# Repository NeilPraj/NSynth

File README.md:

# NSynth
My synthesizer projects.

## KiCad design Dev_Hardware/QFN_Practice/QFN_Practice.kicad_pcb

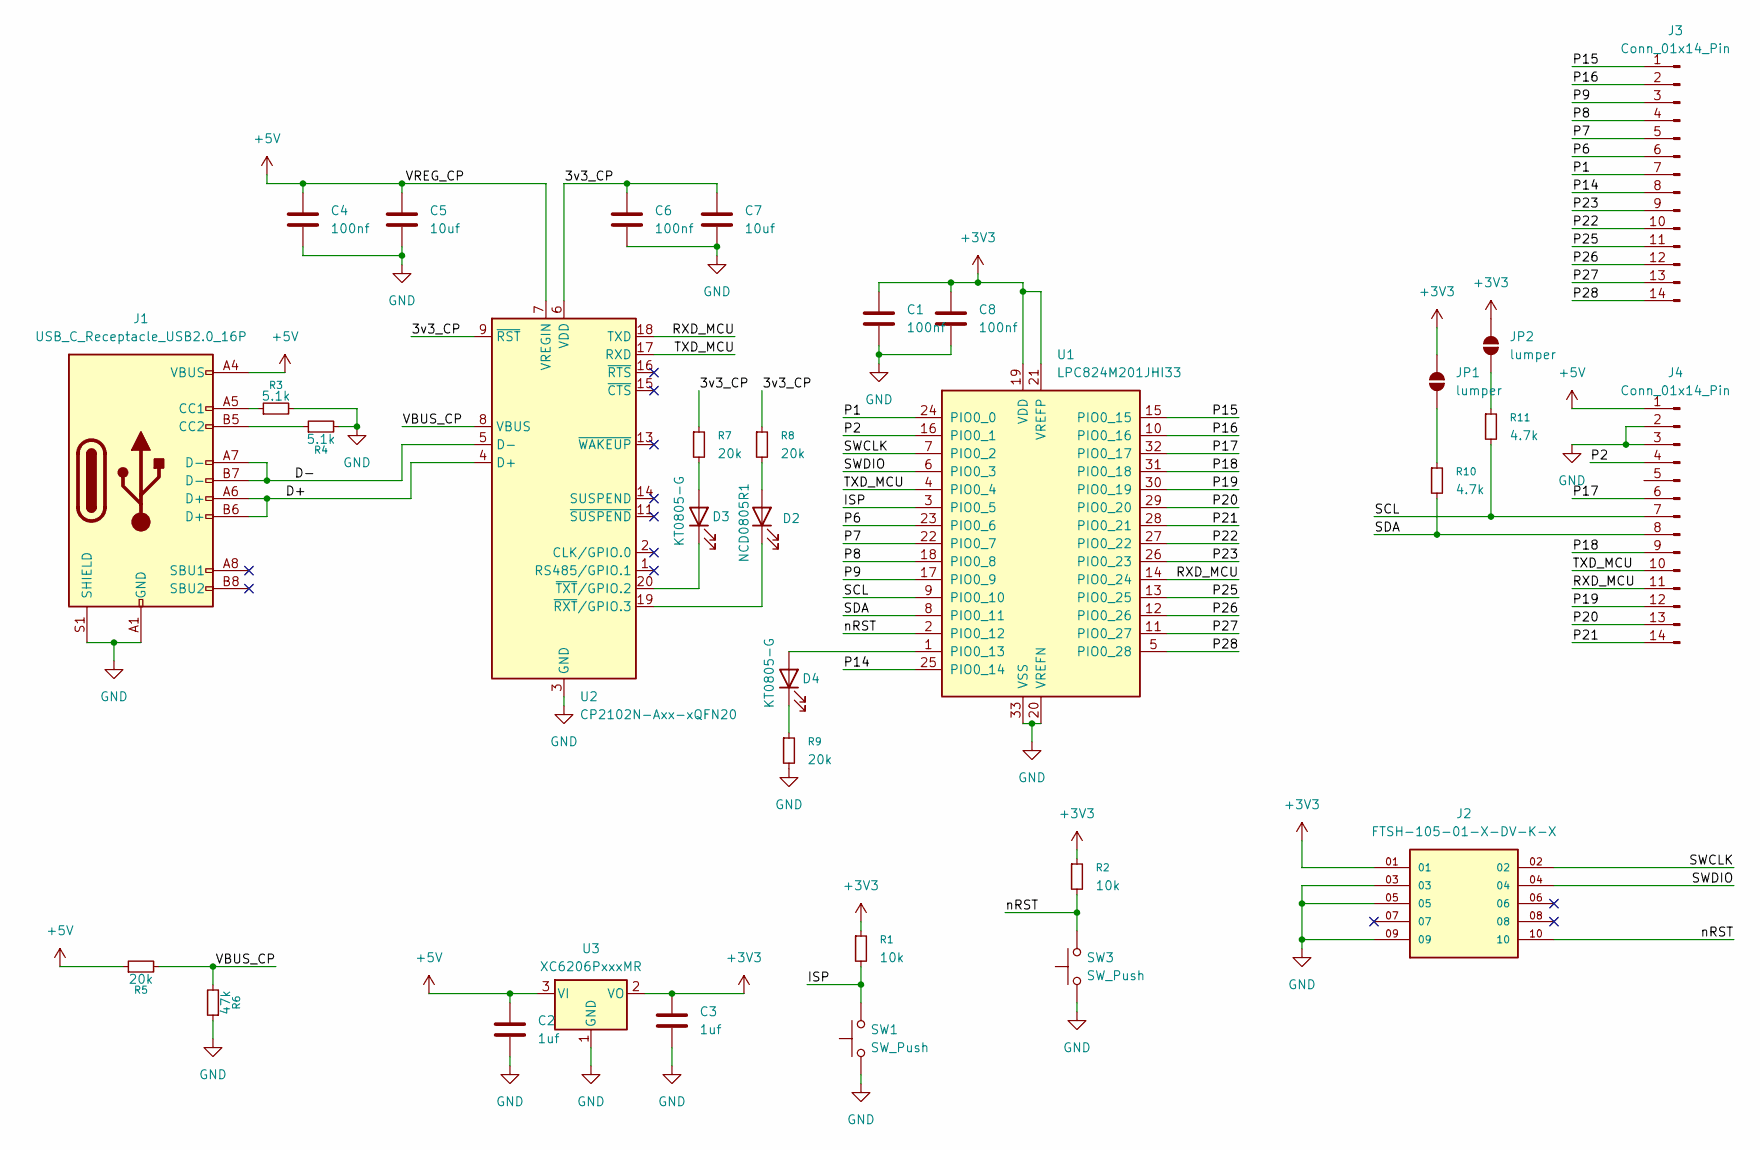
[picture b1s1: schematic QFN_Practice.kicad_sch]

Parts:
C1, C4, C6, C8: 100nf; C_0603_1608Metric
C2, C3: 1uf; C_0603_1608Metric
C5, C7: 10uf; C_0603_1608Metric
D2: NCD0805R1; LED_0805_2012Metric
D3, D4: KT0805-G; LED_0805_2012Metric
J1: USB_C_Receptacle_USB2.0_16P; USB_C_Receptacle_G-Switch_GT-USB-7010ASV
J2: FTSH-105-01-X-DV-K-X; SAMTEC_FTSH-105-01-X-DV-K-X; PARTREV H
J3, J4: Conn_01x14_Pin; PinHeader_1x14_P2.54mm_Vertical
JP1, JP2: lumper; SolderJumper-2_P1.3mm_Open_RoundedPad1.0x1.5mm
R1, R2: 10k; R_0603_1608Metric
R3, R4: 5.1k; R_0603_1608Metric
R5, R7, R8, R9: 20k; R_0603_1608Metric
R6: 47k; R_0603_1608Metric
R10, R11: 4.7k; R_0603_1608Metric
SW1, SW3: SW_Push; SW_SPST_TS-1088-xR020
U1: LPC824M201JHI33; QFN-32-1EP_5x5mm_P0.5mm_EP3.45x3.45mm
U2: CP2102N-Axx-xQFN20; SiliconLabs_QFN-20-1EP_3x3mm_P0.5mm_EP1.8x1.8mm
U3: XC6206PxxxMR; SOT-23-3

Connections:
+3V3: C1.1, C3.1, C8.1, J2.01, JP1.2 (B), JP2.2 (B), R1.1, R2.1, U1.19 (VDD), U1.21 (VREFP), U3.2 (VO)
+5V: C2.1, C4.1, C5.1, J1.A4 (VBUS), J1.A9 (VBUS), J1.B4 (VBUS), J1.B9 (VBUS), J4.1, R5.1, U2.7 (VREGIN), U3.3 (VI)
/3v3_CP: C6.1, C7.1, R7.1, R8.1, U2.6 (VDD), U2.9 (~RST)
/D+: J1.A6 (D+), J1.B6 (D+), U2.4 (D+)
/D-: J1.A7 (D-), J1.B7 (D-), U2.5 (D-)
/ISP: R1.2, SW1.2, U1.3 (PIO0_5)
/P1: J3.7, U1.24 (PIO0_0)
/P2: J4.4, U1.16 (PIO0_1)
/P6: J3.6, U1.23 (PIO0_6)
/P7: J3.5, U1.22 (PIO0_7)
/P8: J3.4, U1.18 (PIO0_8)
/P9: J3.3, U1.17 (PIO0_9)
/P14: J3.8, U1.25 (PIO0_14)
/P15: J3.1, U1.15 (PIO0_15)
/P16: J3.2, U1.10 (PIO0_16)
/P17: J4.6, U1.32 (PIO0_17)
/P18: J4.9, U1.31 (PIO0_18)
/P19: J4.12, U1.30 (PIO0_19)
/P20: J4.13, U1.29 (PIO0_20)
/P21: J4.14, U1.28 (PIO0_21)
/P22: J3.10, U1.27 (PIO0_22)
/P23: J3.9, U1.26 (PIO0_23)
/P25: J3.11, U1.13 (PIO0_25)
/P26: J3.12, U1.12 (PIO0_26)
/P27: J3.13, U1.11 (PIO0_27)
/P28: J3.14, U1.5 (PIO0_28)
/RXD_MCU: J4.11, U1.14 (PIO0_24), U2.18 (TXD)
/SCL: J4.7, R11.2, U1.9 (PIO0_10)
/SDA: J4.8, R10.2, U1.8 (PIO0_11)
/SWCLK: J2.02, U1.7 (PIO0_2)
/SWDIO: J2.04, U1.6 (PIO0_3)
/TXD_MCU: J4.10, U1.4 (PIO0_4), U2.17 (RXD)
/VBUS_CP: R5.2, R6.2, U2.8 (VBUS)
/nRST: J2.10, R2.2, SW3.2, U1.2 (PIO0_12)
GND: C1.2, C2.2, C3.2, C4.2, C5.2, C6.2, C7.2, C8.2, J1.A1 (GND), J1.A12 (GND), J1.B1 (GND), J1.B12 (GND), J1.S1 (SHIELD), J2.03, J2.05, J2.09, J4.2, J4.3, R3.2, R4.2, R6.1, R9.2, SW1.1, SW3.1, U1.20 (VREFN), U1.33 (VSS), U2.3 (GND), U2.12 (GND), U2.21 (GND), U3.1 (GND)
unnamed: D2.2 (A), R8.2
unnamed: D2.1 (K), U2.19 (~RXT/GPIO.3)
unnamed: D3.2 (A), R7.2
unnamed: D3.1 (K), U2.20 (~TXT/GPIO.2)
unnamed: D4.2 (A), U1.1 (PIO0_13)
unnamed: D4.1 (K), R9.1
unnamed: J1.A5 (CC1), R3.1
unnamed: J1.B5 (CC2), R4.1
unnamed: JP1.1 (A), R10.1
unnamed: JP2.1 (A), R11.1

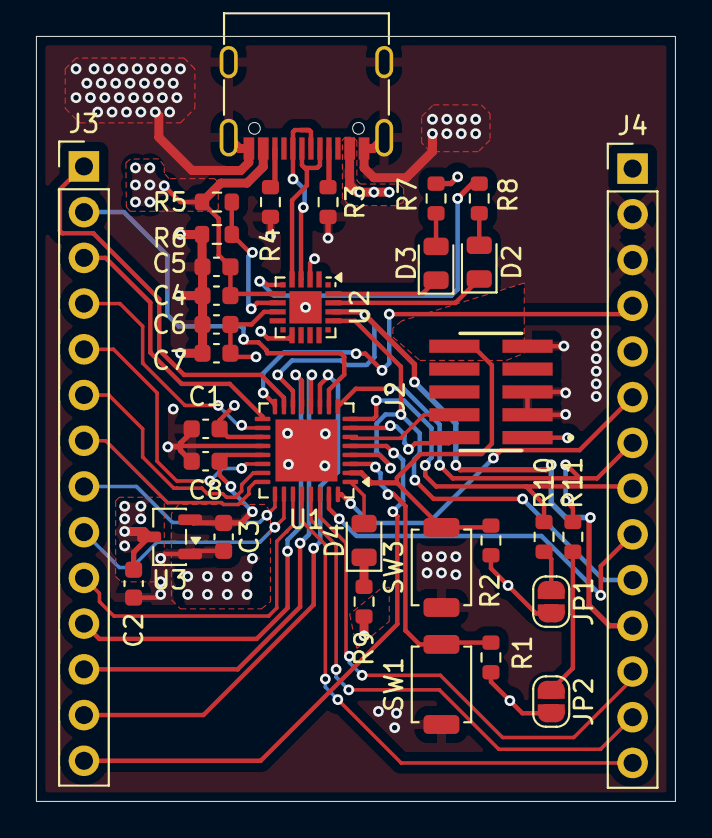
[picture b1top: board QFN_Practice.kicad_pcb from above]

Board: 4 copper layers, 35.5 x 42.5 mm, 33 parts (0 on the bottom side), 45 nets.

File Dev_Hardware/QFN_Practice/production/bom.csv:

Designator,Footprint,Quantity,Value,LCSC Part #
"C1, C4, C6, C8",0603,4,100nf,
"C2, C3",0603,2,1uf,
"C5, C7",0603,2,10uf,
D2,0805,1,NCD0805R1,
"D3, D4",0805,2,KT0805-G,
J1,USB_C_Receptacle_G-Switch_GT-USB-7010ASV,1,USB_C_Receptacle_USB2.0_16P,
J2,SAMTEC_FTSH-105-01-X-DV-K-X,1,FTSH-105-01-X-DV-K-X,
"J3, J4",PinHeader_1x14_P2.54mm_Vertical,2,Conn_01x14_Pin,
"R1, R2",0603,2,10k,
"R10, R11",0603,2,4.7k,
"R3, R4",0603,2,5.1k,
"R5, R7, R8, R9",0603,4,20k,
R6,0603,1,47k,
"SW1, SW3",SW_SPST_TS-1088-xR020,2,SW_Push,
U1,QFN-32-1EP_5x5mm_P0.5mm_EP3.45x3.45mm,1,LPC824M201JHI33,
U2,SiliconLabs_QFN-20-1EP_3x3mm_P0.5mm_EP1.8x1.8mm,1,CP2102N-Axx-xQFN20,
U3,SOT-23-3,1,XC6206PxxxMR,

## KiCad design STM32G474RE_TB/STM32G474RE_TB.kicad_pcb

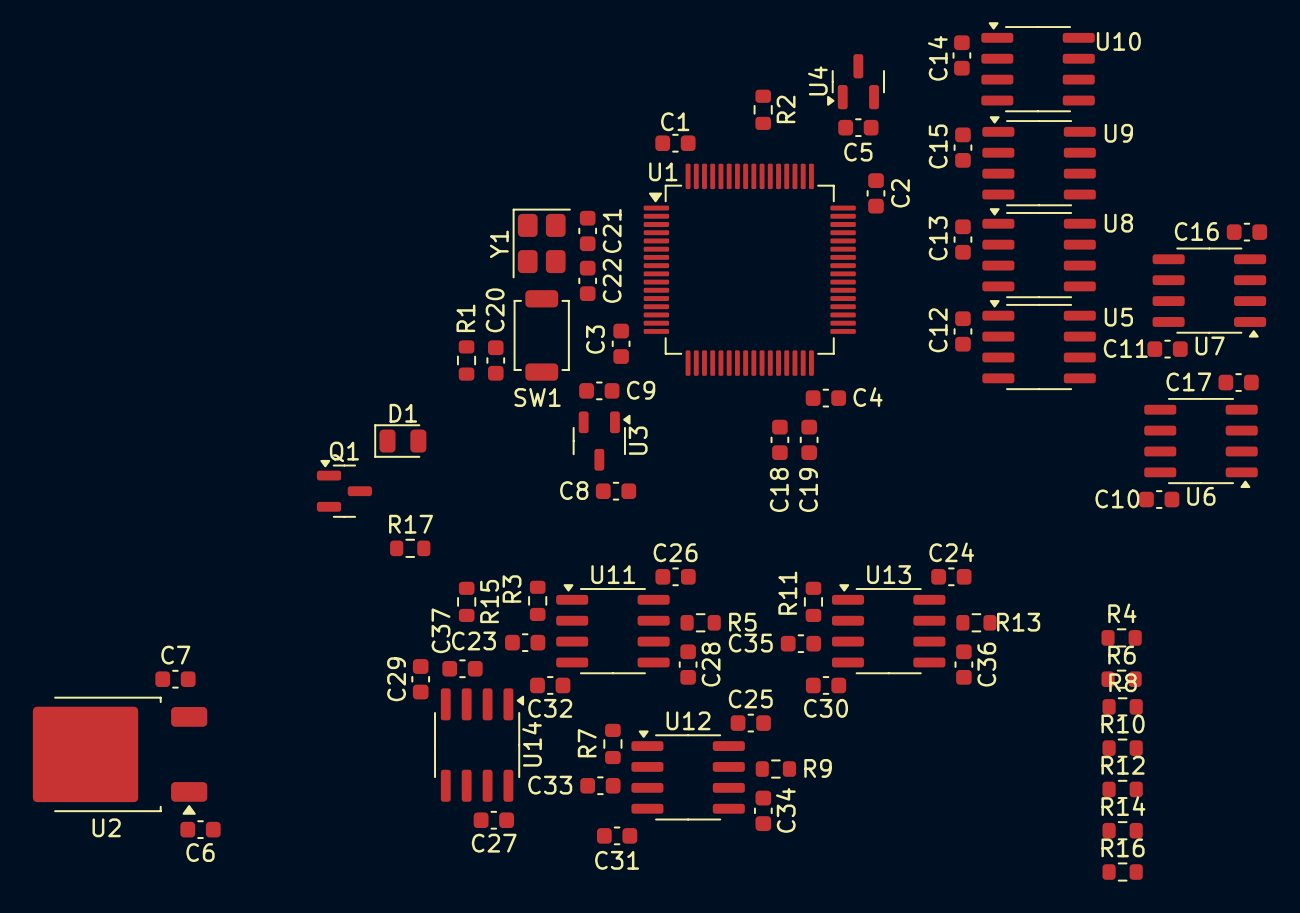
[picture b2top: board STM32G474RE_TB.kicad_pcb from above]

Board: 2 copper layers, 72 parts (0 on the bottom side), 47 nets, no tracks yet.

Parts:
C1, C2, C3, C4: 100nF; C_0603_1608Metric
C5: 0.47uF; C_0603_1608Metric
C6: 0.33uf; C_0603_1608Metric
C7, C10, C11, C12, C13, C14, C15, C16, C17, C18, C20, C24, C25, C26, C27, C29, C30, C31, C32: 0.1uf; C_0603_1608Metric
C8, C9: 1u; C_0603_1608Metric
C19: 1uf; C_0603_1608Metric
C21, C22: 22pf; C_0603_1608Metric
C23, C28, C33, C34, C35: 330nF; C_0603_1608Metric
C36, C37: 33nf; C_0603_1608Metric
D1: XL-2012UBC; LED_0805_2012Metric
Q1: 2N7002; SOT-23
R1: 10k; R_0603_1608Metric
R2: 100k; R_0603_1608Metric
R3, R5, R7, R9, R11, R13, R15, R17: 220; R_0603_1608Metric
R4, R6, R8, R10, R12, R14, R16: 1k; R_0603_1608Metric
SW1: TS-1088-AR02016; SW_SPST_TS-1088-xR025
U1: STM32G474RETx; LQFP-64_10x10mm_P0.5mm
U2: L7805; TO-252-2
U3: XC6206P332MR-G; SOT-23-3
U4: REF3125; SOT-23
U5, U8, U9, U10: MCP4921-ESN; SOIC-8_3.9x4.9mm_P1.27mm
U6, U7, U11, U12, U13, U14: OPA1678; SOIC-8_3.9x4.9mm_P1.27mm
Y1: ABM8G-24.000MHZ-18-D2Y-T; Crystal_SMD_Abracon_ABM8G-4Pin_3.2x2.5mm

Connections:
+2V5REF: C18.1, C19.1, U1.28 (VREF+), U4.2 (OUT), U5.6 (VrefA), U8.6 (VrefA), U9.6 (VrefA), U10.6 (VrefA)
+3.3V: C1.2, C2.2, C3.2, C4.2, C5.1, C9.2, R1.1, U1.1 (VBAT), U1.16 (VDD), U1.29 (VDDA), U1.32 (VDD), U1.48 (VDD), U1.64 (VDD), U3.2 (VO), U4.1 (IN)
+5V: C7.2, C8.2, C12.1, C13.1, C14.1, C15.1, R17.2, U2.3 (OUT), U3.3 (VI), U5.1 (VDD), U8.1 (VDD), U9.1 (VDD), U10.1 (VDD)
+12V: C6.2, C10.1, C11.1, C24.1, C25.1, C26.1, C27.1, U2.1 (IN), U6.8 (V+), U7.8 (V+), U11.8 (V+), U12.8 (V+), U13.8 (V+), U14.8 (V+)
-12V: C16.1, C17.1, C29.1, C30.1, C31.1, C32.1, U6.4 (V-), U7.4 (V-), U11.4 (V-), U12.4 (V-), U13.4 (V-), U14.4 (V-)
/DAC1_CS: U1.38 (PC6), U5.2 (~CS)
/DAC2_CS: U1.39 (PC7), U8.2 (~CS)
/DAC3_CS: U1.40 (PC8), U9.2 (~CS)
/DAC4_CS: U1.41 (PC9), U10.2 (~CS)
/MCU_CONFIG/NRST: C20.1, R1.2, SW1.2, U1.7 (PG10)
/MCU_CONFIG/PD2/BOOT0: R2.2, U1.55 (PD2)
/MCU_CONFIG/XOSC1: C21.1, U1.5 (PF0), Y1.1
/MCU_CONFIG/XOSC2: C22.1, U1.6 (PF1), Y1.3
/SPI1_DACs/DAC1_OUT: U6.1, U6.2 (-)
/SPI1_DACs/DAC1_out_nobuf: U5.8 (VoutA), U6.3 (+)
/SPI1_DACs/DAC2_OUT: U6.6 (-), U6.7
/SPI1_DACs/DAC2_out_nobuf: U6.5 (+), U8.8 (VoutA)
/SPI1_DACs/DAC3_OUT: U7.1, U7.2 (-)
/SPI1_DACs/DAC3_out_nobuf: U7.3 (+), U9.8 (VoutA)
/SPI1_DACs/DAC4_OUT: U7.6 (-), U7.7
/SPI1_DACs/DAC4_out_nobuf: U7.5 (+), U10.8 (VoutA)
/SPI1_MOSI: U1.37 (PB15), U5.3 (SCK), U8.3 (SCK), U9.3 (SCK), U10.3 (SCK)
/SPI1_SCK: U1.35 (PB13), U5.4 (SDI), U8.4 (SDI), U9.4 (SDI), U10.4 (SDI)
/STDAC1_C1_OUT: R3.1, U1.18 (PA4)
/STDAC1_C2_OUT: R5.1, U1.19 (PA5)
/STDAC2_OUT: R7.1, U1.20 (PA6)
/STDAC3_C1_OUT: R9.1, U1.14 (PA2)
/STDAC3_C2_OUT: R11.1, U1.25 (PB1)
/STDAC4_C1_OUT: R13.1, U1.34 (PB12)
/STDAC4_C2_OUT: R15.1, U1.42 (PA8)
GND: C1.1, C2.1, C3.1, C4.1, C5.2, C6.1, C7.1, C8.1, C9.1, C10.2, C11.2, C12.2, C13.2, C14.2, C15.2, C16.2, C17.2, C18.2, C19.2, C20.2, C21.2, C22.2, C23.2, C24.2, C25.2, C26.2, C27.2, C28.2, C29.2, C30.2, C31.2, C32.2, C33.2, C34.2, C35.2, C36.2, C37.2, Q1.2 (S), R2.1, SW1.1, U1.15 (VSS), U1.27 (VSSA), U1.31 (VSS), U1.47 (VSS), U1.63 (VSS), U2.2 (GND), U3.1 (GND), U4.3 (GND), U5.5 (~LDAC), U5.7 (AVSS), U8.5 (~LDAC), U8.7 (AVSS), U9.5 (~LDAC), U9.7 (AVSS), U10.5 (~LDAC), U10.7 (AVSS), Y1.2 (GND), Y1.4 (GND__1)
unnamed: D1.2 (A), R17.1
unnamed: D1.1 (K), Q1.3 (D)
unnamed: C23.1, R3.2, U11.3 (+)
unnamed: R4.1, U11.1, U11.2 (-)
unnamed: C28.1, R5.2, U11.5 (+)
unnamed: R6.1, U11.6 (-), U11.7
unnamed: C33.1, R7.2, U12.3 (+)
unnamed: R8.1, U12.1, U12.2 (-)
unnamed: C34.1, R9.2, U12.5 (+)
unnamed: R10.1, U12.6 (-), U12.7
unnamed: C35.1, R11.2, U13.3 (+)
unnamed: R12.1, U13.1, U13.2 (-)
unnamed: C36.1, R13.2, U13.5 (+)
unnamed: R14.1, U13.6 (-), U13.7
unnamed: C37.1, R15.2, U14.3 (+)
unnamed: R16.1, U14.1, U14.2 (-)

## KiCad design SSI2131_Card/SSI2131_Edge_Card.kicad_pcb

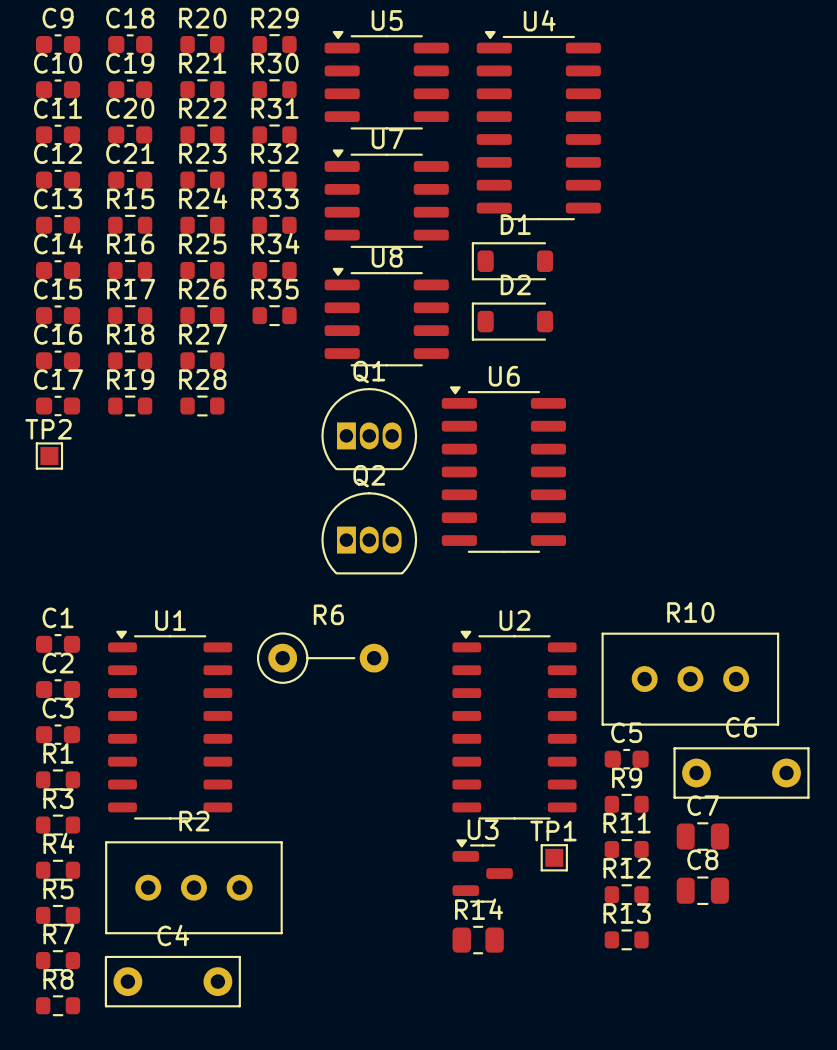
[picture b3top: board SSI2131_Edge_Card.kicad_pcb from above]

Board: 2 copper layers, 70 parts (0 on the bottom side), 43 nets, no tracks yet.

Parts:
C1, C5: 220nF; C_0603_1608Metric
C2, C3: 10n; C_0603_1608Metric
C4, C6: 3.9nf; C_Rect_L7.2mm_W2.5mm_P5.00mm_FKS2_FKP2_MKS2_MKP2
C7, C8: 1uf; C_0805_2012Metric
C9, C18: 1nF; C_0603_1608Metric
C10, C19: 470nF; C_0603_1608Metric
C11, C12, C13, C14, C15, C16, C17, C20, C21: 0.1uf; C_0603_1608Metric
D1, D2: 1N4148W; D_SOD-123
Q1, Q2: 2N3906; TO-92_Inline
R1, R9: 100k; R_0603_1608Metric
R2, R10: 5k; Potentiometer_Bourns_3296W_Vertical
R3, R8, R11, R15, R23: 10k; R_0603_1608Metric
R4, R12: 680; R_0603_1608Metric
R5, R13: 20k; R_0603_1608Metric
R6: 267k; R_Axial_DIN0207_L6.3mm_D2.5mm_P5.08mm_Vertical
R7: 4.3k; R_0603_1608Metric
R14: 2k; R_0805_2012Metric
R16, R24: 2.5k; R_0603_1608Metric
R17, R26: 6.8k; R_0603_1608Metric
R18, R29: 33k; R_0603_1608Metric
R19, R30: 120k; R_0603_1608Metric
R20, R31: 3.9k; R_0603_1608Metric
R21, R22, R25, R27, R28, R32, R33, R34, R35: 1k; R_0603_1608Metric
TP1: 2V5 TP; TestPoint_Pad_1.0x1.0mm
TP2: PMOD_TP; TestPoint_Pad_1.0x1.0mm
U1, U2: SSI2131; STC_SOP-16_3.9x9.9mm_P1.27mm
U3: LM4040DBZ-2.5; SOT-23
U4: LM13700; SOIC-16_3.9x9.9mm_P1.27mm
U5, U7, U8: OPA1678; SOIC-8_3.9x4.9mm_P1.27mm
U6: CD4066BM; SOIC-14_3.9x8.7mm_P1.27mm

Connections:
+2V5: C7.1, C8.1, R1.2, R2.1, R9.2, R10.1, R14.2, TP1.1, U3.1 (K)
+5V: C11.1, C12.1, C13.1, C14.1, C20.1, R14.1, U4.11 (V+), U5.8 (V+), U6.14 (VDD), U7.8 (V+), U8.8 (V+)
-12V: C15.1, C16.1, C17.1, C21.1, U4.6 (V-), U5.4 (V-), U7.4 (V-), U8.4 (V-)
/B_EXPO_IN: R9.1, R11.2, R13.2, U2.6 (EXPO_FREQ)
/OSC A/A_EXPO_IN: R1.1, R3.2, R6.2, R18.2, TP2.1, U1.6 (EXPO_FREQ), U5.7
/OSC A/PWM_MOD_IN: R27.2, U8.1
GND: C1.2, C4.2, C5.2, C7.2, C8.2, C11.2, C12.2, C13.2, C14.2, C15.2, C16.2, C17.2, C20.2, C21.2, R2.3, R7.1, R8.1, R10.3, R21.1, R22.1, R34.1, R35.1, U3.2 (A), U5.3 (+), U5.5 (+), U6.7 (VSS), U7.3 (+), U7.5 (+), U8.3 (+), U8.5 (+)
unnamed: C1.1, R4.2, R5.1
unnamed: C5.1, R12.2, R13.1
unnamed: C10.1, U6.2
unnamed: C10.2, R19.1
unnamed: C19.1, U6.3
unnamed: C19.2, R30.1
unnamed: C9.2, D1.2 (A), Q1.1 (E)
unnamed: C9.1, D1.1 (K), R16.1, U5.2 (-)
unnamed: C18.2, D2.2 (A), Q2.1 (E)
unnamed: C18.1, D2.1 (K), R24.1, U7.2 (-)
unnamed: Q1.2 (B), U5.1
unnamed: Q1.3 (C), R17.1
unnamed: Q2.2 (B), U7.1
unnamed: Q2.3 (C), R26.1
unnamed: R2.2, R3.1
unnamed: R10.2, R11.1
unnamed: R15.1, R16.2
unnamed: R17.2, U4.16
unnamed: R19.2, R20.1
unnamed: R23.1, R24.2
unnamed: R26.2, U4.1
unnamed: R28.2, R32.1, U8.7
unnamed: R29.2, R33.2, U7.7
unnamed: R30.2, R31.1
unnamed: C3.2, R8.2, U1.10 (HARD_SYNC)
unnamed: R6.1, R7.2, U1.5 (HF_TRACK)
unnamed: C2.2, U1.11 (SOFT_SYNC)
unnamed: C4.1, U1.8 (TCAP)
unnamed: R22.2, U4.14 (+)
unnamed: R20.2, R21.2, U4.13 (-)
unnamed: R35.2, U4.3 (+)
unnamed: R31.2, R34.2, U4.4 (-)
unnamed: R18.1, U4.12, U5.6 (-)
unnamed: R29.1, U4.5, U7.6 (-)
unnamed: R27.1, R32.2, U8.2 (-)
unnamed: R25.2, R28.1, R33.1, U8.6 (-)

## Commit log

2025-11-25 SSI2131 Edge card connector init
2025-11-26 renamed file
2025-11-26 Aded Heiarchy in Kicad, adjusted overall VCA design
2025-11-26 Added pin lables and added VCOs into their own heiarchy sheets
2025-11-26 adjusted PCB layout for new haiarchy
2025-11-27 Added Biasing for CD4066 switches. Added biasing pot for PWM mod.
2025-12-01 added connections for lfo adn pmod
2025-12-01 added test board for STM32G4 series of mcu's. Need to test env and LFO signal generation as well as DAC tuning over SPI
2025-12-01 Rotated STM32 and adjusted xosc capacitor values.
2025-12-01 Added temporary STM32Cubeide project for pin config.
2025-12-02 Added power LDO and built DAC buffer circuits Added pin descriptions
2025-12-05 Adjusted layouts and added DAC buffer from stm32.
2025-12-21 Added MOSFET template with led for debug or other functions
2026-01-11 adjusted colors for readbility
2026-01-24 added QFN practice PDB
2026-01-28 added pin defs to qfn_test
2026-01-30 Added USB wiring and power wiring
2026-02-02 Finish schematics for QFN board, started routing USB
2026-02-08 finished routing for all but power regulation and GPIO
2026-02-10 finished layout
2026-02-16 routed more of the QFN test pcb
2026-02-17 finished layout and routing
2026-02-18 added outputs
2026-03-22 finished QFN dev board
